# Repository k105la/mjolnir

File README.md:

# mjolnir
Hardware keylogger based around the ATtiny85 with the micronucleus firmware. 

## Usage 
```
cd ~/mjolnir/firmware && ./flash_mjolnir.sh
```

Directory Structure
------
    .
        
    ├── Mjolnir-PCB         # Eagle CAD PCB files
    ├── examples            # The example code 
    └── firmware            # Firmware for ATtiny85

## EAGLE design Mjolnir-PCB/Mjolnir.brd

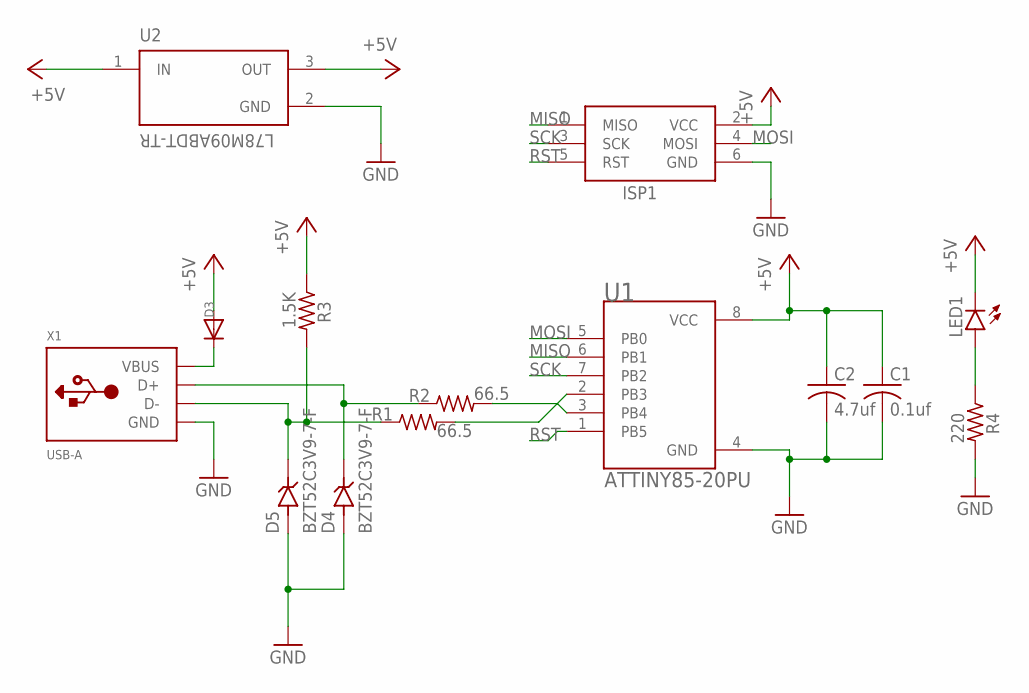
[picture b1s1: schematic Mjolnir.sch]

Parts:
C1: 0.1uf; C0805
C2: 4.7uf; C0805
D3: DIODESOD-123; SOD-123
D4, D5: BZT52C3V9-7-F; SOD3715X145N
ISP1: AVRISP-6; AVRISP
LED1: LEDCHIPLED_0805; CHIPLED_0805
R1, R2: 66.5; R0805
R3: 1.5K; R0805
R4: 220; R0805
U1: ATTINY85-20PU; DIP762W46P254L927H533Q8B
U2: L78M09ABDT-TR; VREG_L78M09ABDT-TR
X1: USB-A; MOLEX_480371000

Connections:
+5V: C1.1, C2.1, D3.A, ISP1.2 (VCC), LED1.C, R3.1, U1.8 (VCC), U2.1 (IN), U2.3 (OUT)
GND: C1.2, C2.2, D4.A, D5.A, ISP1.6 (GND), R4.2, U1.4 (GND), U2.2 (GND), X1.4 (GND)
MISO: ISP1.1 (MISO), U1.6 (PB1)
MOSI: ISP1.4 (MOSI), U1.5 (PB0)
unnamed: LED1.A, R4.1
unnamed: D3.C, X1.1 (VBUS)
unnamed: D5.C, R1.1, R3.2, X1.2 (D-)
unnamed: R2.2, U1.3 (PB4)
unnamed: D4.C, R2.1, X1.3 (D+)
unnamed: R1.2, U1.2 (PB3)
RST: ISP1.5 (RST), U1.1 (PB5)
SCK: ISP1.3 (SCK), U1.7 (PB2)

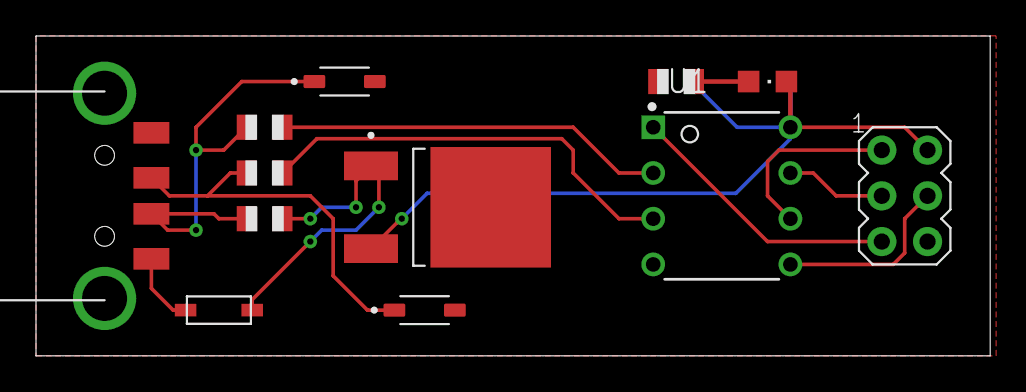
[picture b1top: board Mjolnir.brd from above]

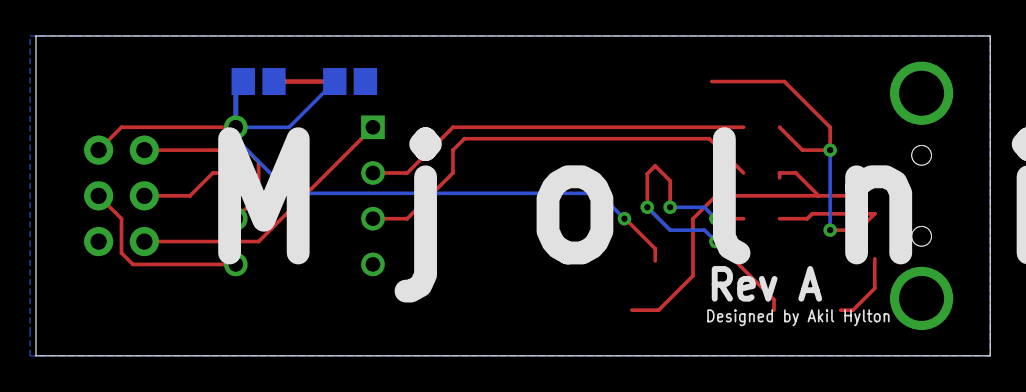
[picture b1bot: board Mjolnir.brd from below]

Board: 2 copper layers, 53.0 x 17.8 mm, 14 parts (2 on the bottom side), 12 nets.

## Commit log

2021-06-04 micronucleus firmware for ATtiny85
2021-06-19 Eagle PCB files
2021-06-19 Replaced zener diodes to SOD-123 footprint
2021-06-19 Updated PCB files
2021-06-19 Created parts list
2021-08-01 Bash script to flash mjolnir hardware
2021-08-18 Programmer can now be changed in the flash_mjolnir script
